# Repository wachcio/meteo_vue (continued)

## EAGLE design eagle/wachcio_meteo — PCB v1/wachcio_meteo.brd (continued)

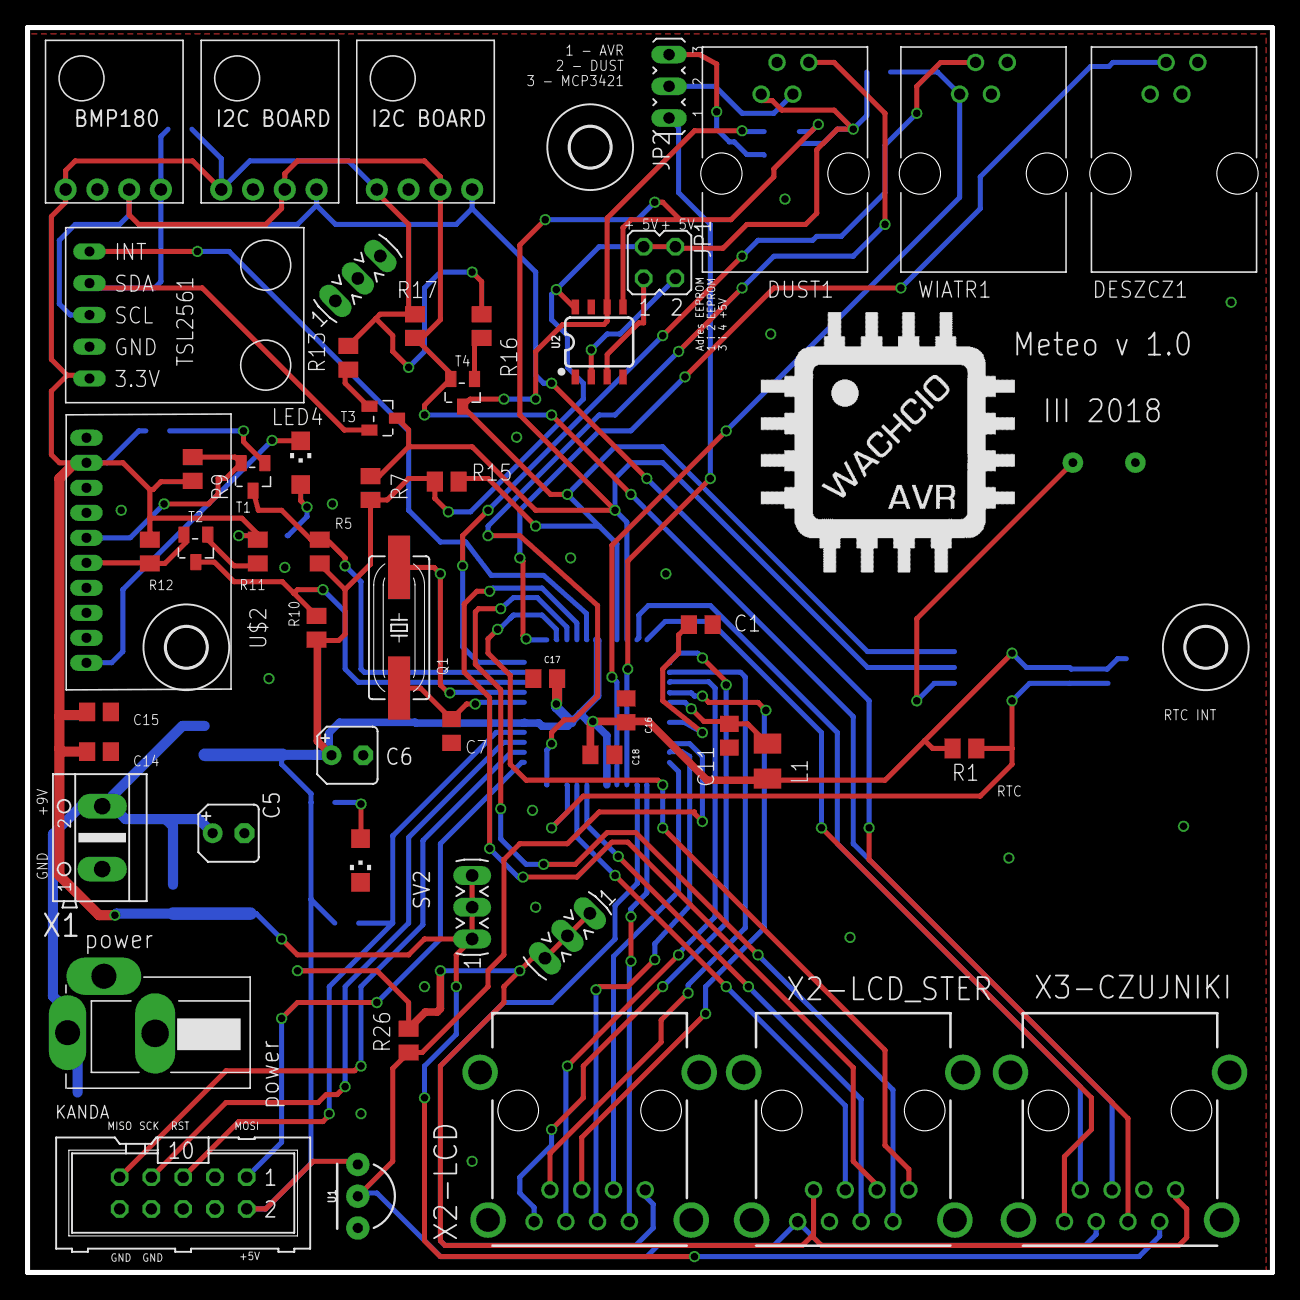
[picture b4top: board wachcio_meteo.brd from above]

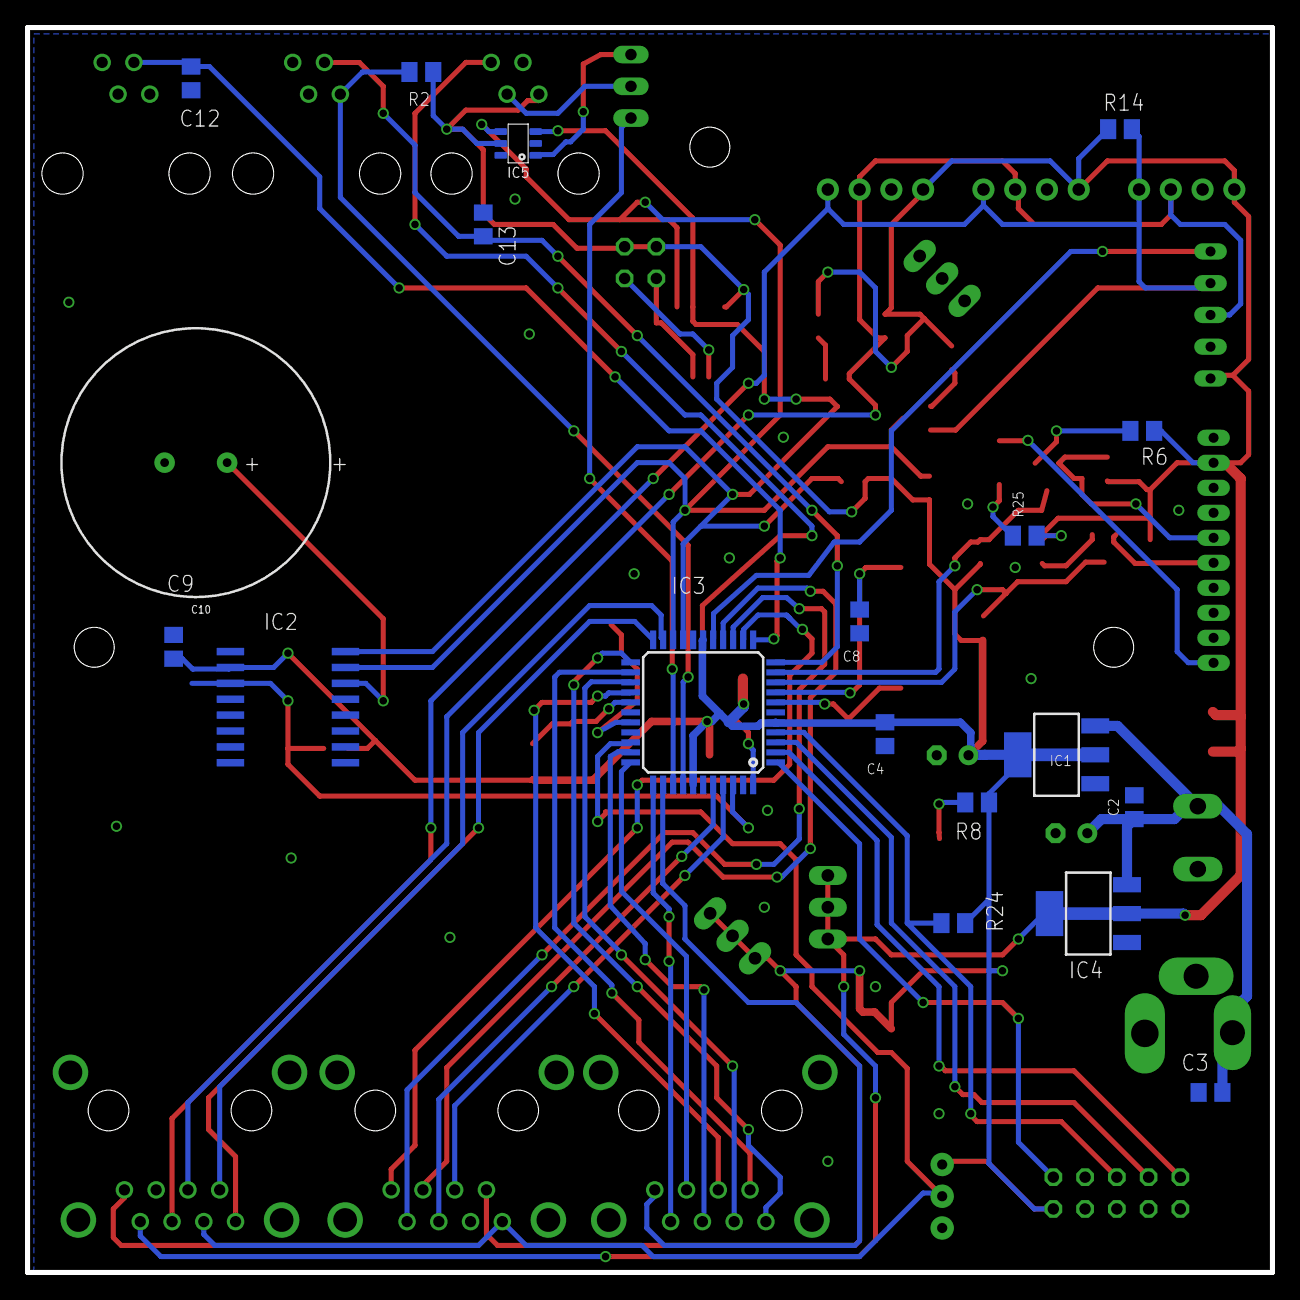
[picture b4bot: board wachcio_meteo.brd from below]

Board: 2 copper layers, 99.6 x 99.6 mm, 74 parts (19 on the bottom side), 55 nets.

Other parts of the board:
U$8: LOGO

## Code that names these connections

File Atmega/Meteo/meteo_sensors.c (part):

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

//Sposób pod³¹czenia
//opady - PD3 i GND
//kierunek wiatru - PA0, GND i przez rezystor VCC
//prêdkoc wiatru PD2 i GND

// zmienne - wiatr (1 impuls na 1 sek = 2,4km/h)
//volatile uint32_t tmp_spd_wind;                                //licznik impulsów z czujnika prêdkoci wiatru
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                tpstr.delim2 = d2php;
                tpstr.d2len = strlen( d2php );
                operacja = _ip2;
//PORTD ^= (1<<PD6);
//                P1=rand();
//                P2=rand();
//                P3=rand();
//                P4=rand();
// http://meteo.wachcio.pl/pogoda_test/index.php?TOKEN=7894561230&predkosc_wiatru=1&poryw_wiatru=1&kierunek_wiatru=1&opady=1&temperatura=1&temperatura2=1

//                uart_puts( "GET http://delphi-archiwum.home.pl/wachcio/pogoda_test/index.php?TOKEN=7894561230&predkosc_wiatru=" );
                uart_puts( "GET http://meteo.wachcio.pl/API/addSensorsAVR.php?TOKEN=7894561230&predkosc_wiatru= " );
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}

void init_sensors (void) {
//    PORTC ^= (1<<PC3);
    tik=sekundy_pomiaru;
    rainfall_mm = 0;
    spd_wind_kmh_max = 0;
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

    // inicjalizacja przerwania INT0 na potrzeby zliczania impulsów z czujnika wiatru
    PORTD |= (1<<PD2) | (1<<PD3);            // podci¹gniêcie pinu INT0 do VCC
    MCUCR |= (1<<ISC01);            // wyzwalanie zboczem opadaj¹cym
    MCUCR |= (1<<ISC11);            // wyzwalanie zboczem opadaj¹cym
    GICR |= (1<<INT0);            // odblokowanie przerwania
    GICR |= (1<<INT1);            // odblokowanie przerwania

        // Przerwanie INT2
        PORTB |=(1<<PB2);       // pull up's na wejciu INT2
        MCUCSR &=~(1<<ISC2);    // przerwanie na zboczu opadaj¹cym
        GICR |=(1<<INT2);       // w³¹czenie przerwania zewnêtrznego

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//Obs³uga przerwania INT 0 pomiar prêdkoci wiatru
ISR (INT0_vect)  {

//    PORTD &= ~(1<<PD7);
    tmp_spd_wind++;                // przy ka¿dym zboczu opadaj¹cym zlicz impuls

}
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


//    PORTD ^= (1<<PD6);
    tmp_imp_rainfall++;            // przy ka¿dym zboczu opadaj¹cym zlicz impuls
    opady_imp++;

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
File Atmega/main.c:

/*
 * main.c
 *
 *  Created on: 14 pa 2016
 *      Author: avrtech
 *      Strona www: http://avrtech.pl
 *
 *      Obs³uga czujników dla u¿ytku prywatnego wymaga pozostawienia stopki.
 *      Aby wykorzystaæ bibliotekê do celów komercyjnych proszê o kontakt poprzez stronê www.
 */


// DO£¥CZENIE STANDARDOWYCH BIBLIOTEK
#include <avr/io.h>
#include <avr/interrupt.h>
#include <util/delay.h>
#include <avr/pgmspace.h>
#include <inttypes.h>
#include <stdlib.h>
#include <stdio.h>
#include <string.h>
#include <avr/eeprom.h>
#include <avr/wdt.h>

#include "LCD/lcd44780.h"
#include "Meteo/meteo_sensors.h"
#include "MK_USART/mkuart.h"
#include "MK_TERMINAL/mk_term.h"
#include "1Wire/ds18x20.h"
#include "I2C_TWI/i2c_twi.h"
#include "DS3231/DS3231.h"

#define DEBUG1 (1<<PC2)
#define DEBUG1_ON PORTC |= DEBUG1    // makrodefinicja  za³¹czenie diody
#define DEBUG1_OFF PORTC &= ~DEBUG1    // makrodefinicja  wy³¹czenie diody
#define DEBUG1_TOG PORTC ^= DEBUG1    // makrodefinicja  zmiana stanu diody

#define DEBUG2 (1<<PC3)
#define DEBUG2_ON PORTC |= DEBUG2    // makrodefinicja  za³¹czenie diody
#define DEBUG2_OFF PORTC &= ~DEBUG2    // makrodefinicja  wy³¹czenie diody
#define DEBUG2_TOG PORTC ^= DEBUG2    // makrodefinicja  zmiana stanu diody


char uart_buf[100];    //bufor UART

void parse_rs232(char * buf);

int main(void){
    flaga_wyslij_dane =0;



    DDRC |= (1<<PC4);    // ustawiamy kierunek linii podwietlenia LCD jako WYJCIE
    PORTC |= (1<<PC4);    // za³¹czamy podwietlenie LCD - stan wysoki
    DDRA |= (1<<PA7);
    PORTA |= (1<<PA7);


    DDRC |= DEBUG1;    // Debug 1
//    PORTC |= DEBUG1;    //

    DDRC |= DEBUG2;    // Debug 2
//    PORTC |= DEBUG2;    //

    DDRD |= (1<<PD7);        // kierunek pinów PD6 i PD7  wyjciowy
    PORTD |= (1<<PD7);

    PORTB |= NLINK_PIN;

    init_sensors();

//    lcd_init();
//    lcd_locate(0,0);

//    UART
    USART_Init( __UBRR);
            register_uart_str_rx_event_callback(parse_rs232);
//
//    tr_cursor_hide(1);
//        tr_locate(1,0);
//        uart_puts ("Prêdkoæ wiatru: ");
//        uart_putint(spd_wind_kmh_d, 10);
//        uart_puts (",");
//        uart_putint(spd_wind_kmh_j, 10);
//        uart_puts ("km/h");
//
        // Przerwanie INT2
        PORTB |=(1<<PB2);       // pull up's na wejciu INT2
        MCUCSR &=~(1<<ISC2);    // przerwanie na zboczu opadaj¹cym
        GICR |=(1<<INT2);       // w³¹czenie przerwania zewnêtrznego



//            // Przerwanie INT2
//                    MCUCR |= (1<<ISC01)|(1<<ISC00); // zbocze narastaj¹ce
//                    PORTB |= (1<<PB2);        // podci¹gniêcie pinu INT2 do VCC
//
    //RTC DS3231


        i2cSetBitrate(100);
        DS3231_init();



//    lcd_str("Wiatr: ");
//
//        lcd_init();
//        lcd_locate(1,10);
//        lcd_str("K:           ");

    /* sprawdzamy ile czujników DS18xxx widocznych jest na magistrali */
        czujniki_cnt = search_sensors();

        /* wysy³amy rozkaz wykonania pomiaru temperatury
         * do wszystkich czujników na magistrali 1Wire
         * zak³adaj¹c, ¿e zasilane s¹ w trybie NORMAL,
         * gdyby by³ to tryb Parasite, nale¿a³oby u¿yæ
         * jako pierwszego prarametru DS18X20_POWER_PARASITE */
        DS18X20_start_meas( DS18X20_POWER_EXTERN, NULL );

        /* czekamy 750ms na dokonanie konwersji przez pod³¹czone czujniki */
            _delay_ms(750);

//    sekundy_pomiaru = 60;
     sekundy_pomiaru = 5;

 sei();                  // w³¹czenie przerwañ globalnych

    while(1){

//        DEBUG1_TOG;


        UART_RX_STR_EVENT(uart_buf);
           pomiar_temperatury ();

         if (   flaga_wyslij_dane == 1) {
//       wyslij_na_RS232();
//uart_puts ("wachcio");

//wyslij_dane_na_serwer (suma_imp_wiatr, poryw_wiatru_imp, dominanta_liczba, opady_imp, temperatura[1], temperatura[2]);

          }



//        wyslij_dane_na_serwer (suma_imp_wiatr, poryw_wiatru_imp, dominanta_liczba, opady_imp, temperatura[1], temperatura[2]);



    }
}

void parse_rs232(char * buf){

    if( !strncasecmp("AT+RST?", buf, 7) ) {
        cli();              // disable interrupts
        wdt_enable( 0 );      // set  watchdog
        while(1);           // wait for RESET
    }

    if( !strncasecmp("wachcio", buf, 7) ) {
        uart_puts ("ok-wachcio");
        }

      if( !strncasecmp("tog1", buf, 7) ) {
             DEBUG1_TOG;
        }

     if( !strncasecmp("tog2", buf, 7) ) {
             DEBUG2_TOG;
        }
}

ISR(INT2_vect) {

//            DEBUG2_TOG;
         DEBUG1_TOG;
//          uart_puts ("ok-wachcio");
//wyslij_na_RS232();
//            uart_putint(czujniki_cnt, 10);




}

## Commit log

2018-12-08 Create Sensor component
2018-12-09 Cleaning component Sensor
2018-12-09 Add JSON read data
2018-12-09 Add SensorCategory
2018-12-09 Fixed css to SensorCatagory
2018-12-09 Fixed value of sensor
2018-12-09 Add refresh function
2018-12-10 Fixed CSS and display data
2018-12-10 Add air quality widget
2018-12-10 Show info working but need changes
2018-12-12 Show info hide on click and scroll working
2018-12-13 Add preloader, error class and mouseover title
2018-12-13 Info transition
2018-12-13 Hide nav buttons
2018-12-13 Fixed info from rain and wind direction
2018-12-13 Remove from Git hideSettings
2018-12-13 Remove from Git hideSettings v2
2018-12-13 Start working on archive data
2018-12-13 Active buttons in nav
2018-12-13 Add archives section
2018-12-14 Add form archives - not finish
2018-12-15 Form get and parse correct JSON
2018-12-15 Form date ok
2018-12-15 Archives ok
2018-12-15 Add rain sum
2018-12-15 Fixed show wind direction and rain
2018-12-15 Ficed bug whit opady and kierunek wiatru sensor
2018-12-16 Fixed bugs
2018-12-16 Add auto refresh app
2018-12-16 Add footer
2018-12-17 Add 'bezwietrznie' state in wind direction sensor
2018-12-17 Fix bug 'bezwietrznie'
2018-12-17 Fix bug 'bezwietrznie'2
2018-12-18 Use <component> to show and hide components
2018-12-18 Change font-size in body
2018-12-18 Add transition. Have bug when hide every section
2018-12-18 Add AnimateCSS and use this library
2018-12-18 Create AnimateCSS component. Component use Animate CSS
2018-12-18 Start use SCSS
2018-12-19 Add router-view
2018-12-19 Add router-view2
2018-12-20 Add router-view. Works fine. Add new section About. Empty yet
2018-12-20 Start working whit Vuex
2018-12-20 Add store
2018-12-20 Install lodash
2018-12-21 Working whit Vuex in progress
2018-12-21 Working whit Vuex in progress 2
2018-12-21 Working whit Vuex in progress 3
2018-12-21 Application Vuex done
2018-12-21 Small bugs in About.vue
2018-12-21 Fixed small bugs whit isLoaded mutation
2018-12-22 Fixed problem whit show/hide sensor category
2018-12-22 Move animate.css to component catalog
2018-12-23 When wind Speed is 0 then change sensor picture and value
2018-12-23 Fixed problem whit isLoaded
2018-12-23 Fixed problem error class
2018-12-28 Fixed CSS in Air Quality Widget
2018-12-29 Write text
2018-12-31 Fixed small bugs
2018-12-31 Fixed show current sensors on load
2018-12-31 Fixed css in form archive
2019-01-01 Add Flux slider
2019-01-01 Add source map
2019-01-01 Small chenges
2019-01-01 Add dist to Bitbucket
2019-01-01 Add deploy script
2019-01-01 Change gitignore
2019-01-01 Change gitignore2
2019-01-01 Change gitignore3
2019-01-01 Change gitignore4
2019-01-01 Change gitignore5
2019-01-01 Change gitignore6
2019-01-04 Change foter date
2019-01-04 Add alarm min and max to table sensors
2019-01-04 Split sensors.php
2019-01-04 Return alarms in JSON
2019-01-05 Alarms working
2019-01-05 Fixed CSS for mobile
2019-01-06 Add css to scrollbar
2019-01-13 CSS change and add upToDate sensor in JSON
2019-05-21 cleaning
2022-09-08 Update README.md
    Update README
2022-09-08 Update README.md
    Delete backticks
2022-09-08 Update README.md
    Fix header
2022-09-08 Create README.md
    Create eagle folder and readmy
2022-09-08 Add files via upload
    Add files Eagle PCB project
